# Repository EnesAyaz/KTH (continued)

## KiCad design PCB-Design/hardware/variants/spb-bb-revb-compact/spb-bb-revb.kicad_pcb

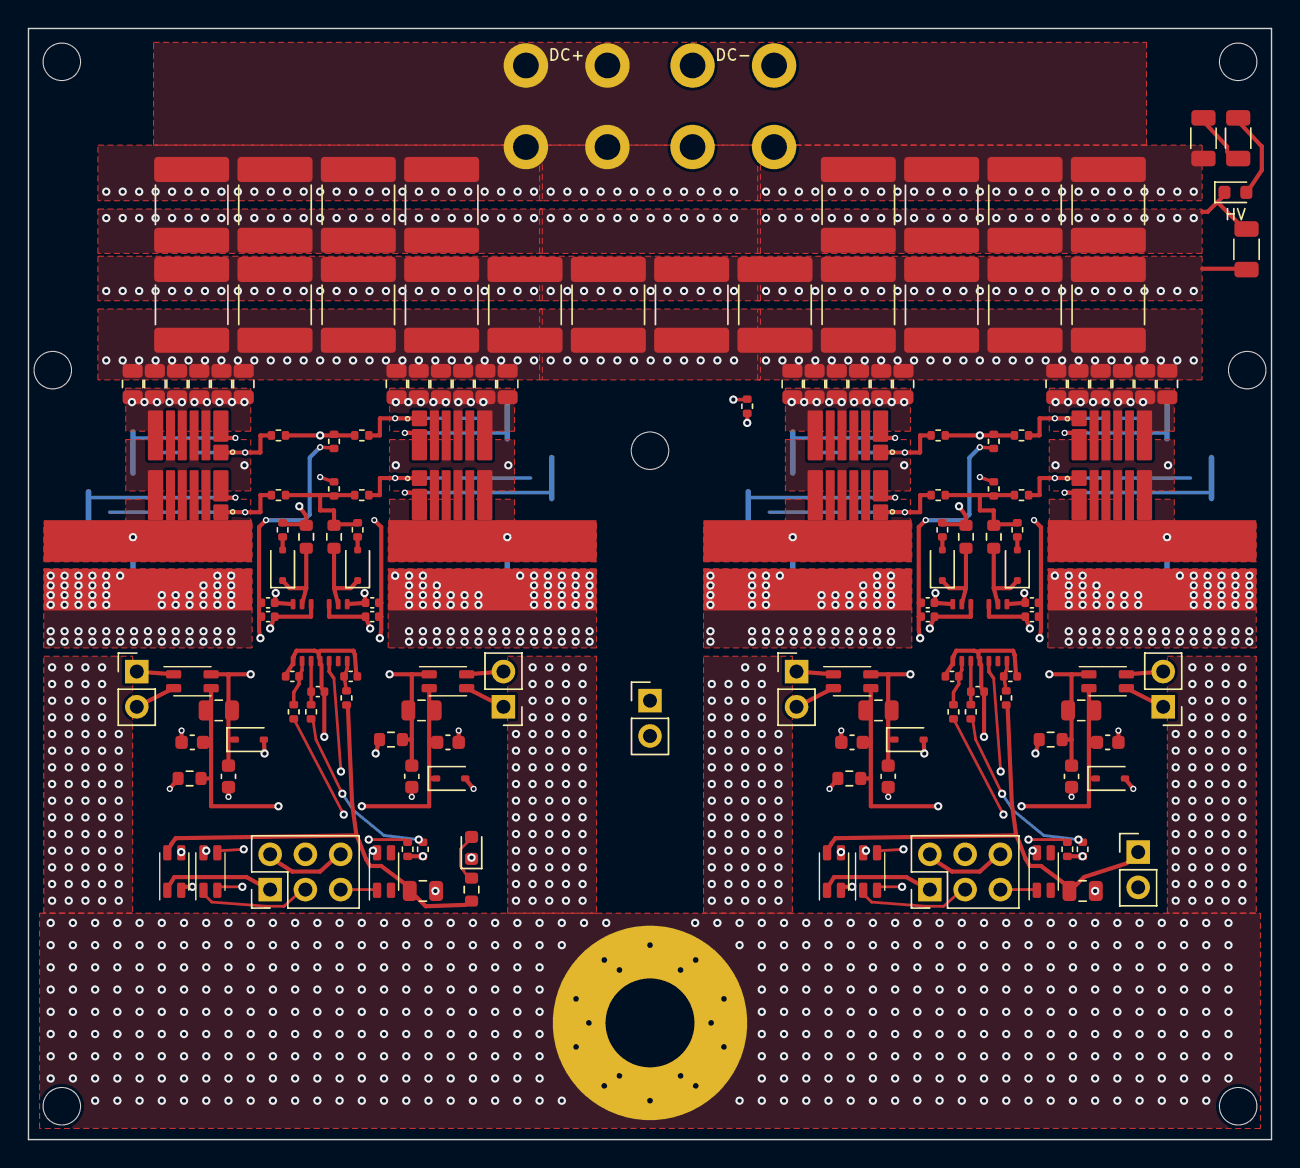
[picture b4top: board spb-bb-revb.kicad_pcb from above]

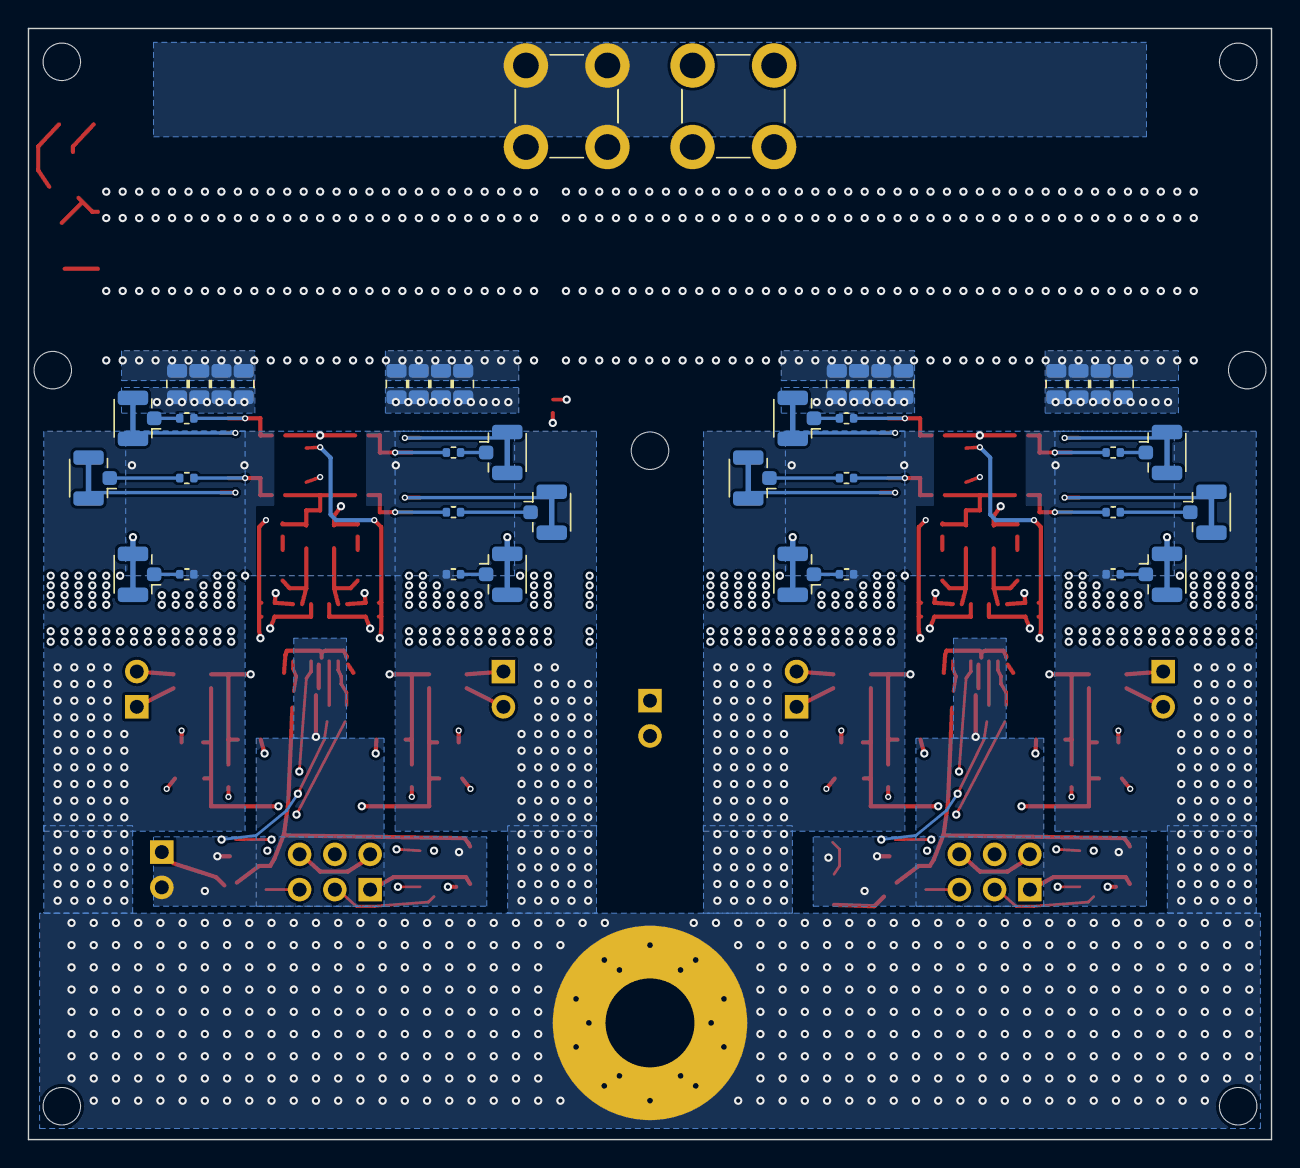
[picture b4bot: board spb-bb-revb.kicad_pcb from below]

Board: 4 copper layers, 89.5 x 80.0 mm, 204 parts (42 on the bottom side), 89 nets.

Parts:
C1, C2, C3, C4, C5, C6, C7, C8, C9, C10, C11, C12, C27, C28, C29, C30, C31, C32, C33, C34, C35, C36, C37, C38, C39, C40, C41, C42, C43, C44, C45, C46, C61, C62, C63, C64, C65, C66, C67, C68: 1uF 100V X7S; C_0805_2012Metric_TightCrtYd
C13, C14, C15, C16, C47, C48, C49, C50: 1uF 16V X7R 0402; C_0402_1005Metric
C17, C18, C51, C52: 100pF C0G 0402; C_0402_1005Metric
C19, C53: 22nF 25V X7R 0402; C_0402_1005Metric
C20, C23, C54, C57: 4.7uF 25V X7R 0805; C_0805_2012Metric
C21, C22, C24, C25, C55, C56, C58, C59: 4.7uF 16V X5R 0603; C_0603_1608Metric
C26, C60: 4.7uF 25V X7R 0805 (12 V); C_0805_2012Metric
C69, C70, C71, C72, C73, C74, C75, C76, C77, C78, C79, C80, C81, C82, C83, C84, C85, C86, C87, C88: 22uF 100V X7S 2220; C_2220_5750Metric_TightCrtYd
D1, D2, D6, D7: PMEG3020EJ; D_SOD-323F
D3, D4, D8, D9: BZX384-C5V1; D_SOD-323
D5: green 0603 (12 V); LED_0603_1608Metric
D10: red 0603 (DC link present); LED_0603_1608Metric
H1, H2, H3, H4: M2.5 insulated; MountingHole_2.7mm_M2.5
H5, H6, H7: M2.5 heatsink spreader; MountingHole_2.7mm_M2.5
HS1: Fischer LAM 4 (100 mm) + spreader; HS_LAM4K10012_revb
J1: DC+; Wuerth_REDCUBE-THR_WP-THRBU_74650174_THR
J2: DC-; Wuerth_REDCUBE-THR_WP-THRBU_74650174_THR
J3, J12: V_ISO,HS in: 1 +, 2 -; PinHeader_1x02_P2.54mm_Vertical
J4, J13: V_ISO,LS in: 1 +, 2 -; PinHeader_1x02_P2.54mm_Vertical
J5: CTRL1: 1 12V 2 GND 3 PWM_H 4 PWM_L 5 DIS 6 GND; PinHeader_2x03_P2.54mm_Vertical
J6: U.FL H1; U.FL_Hirose_U.FL-R-SMT-1_Vertical
J7: U.FL L1; U.FL_Hirose_U.FL-R-SMT-1_Vertical
J8: U.FL D1; U.FL_Hirose_U.FL-R-SMT-1_Vertical
J9: U.FL H2; U.FL_Hirose_U.FL-R-SMT-1_Vertical
J10: U.FL L2; U.FL_Hirose_U.FL-R-SMT-1_Vertical
J11: U.FL D2; U.FL_Hirose_U.FL-R-SMT-1_Vertical
J14: CTRL2: 1 12V 2 GND 3 PWM_H 4 PWM_L 5 DIS 6 GND; PinHeader_2x03_P2.54mm_Vertical
J15: FAN 12V: 1 +12V, 2 GND; PinHeader_1x02_P2.54mm_Vertical
J16: U.FL H3; U.FL_Hirose_U.FL-R-SMT-1_Vertical
J17: U.FL L3; U.FL_Hirose_U.FL-R-SMT-1_Vertical
J18: U.FL D3; U.FL_Hirose_U.FL-R-SMT-1_Vertical
J19: U.FL H4; U.FL_Hirose_U.FL-R-SMT-1_Vertical
J20: U.FL L4; U.FL_Hirose_U.FL-R-SMT-1_Vertical
J21: U.FL D4; U.FL_Hirose_U.FL-R-SMT-1_Vertical
J22: AC; AC_BOLT_M6
J23: 1:NTC 2:DC- (LS domain!); PinHeader_1x02_P2.54mm_Vertical
L1, L2, L3, L4, L5, L6, L7, L8, L9, L10: WE-CNSW 744232601; L_CommonMode_Wurth_WE-CNSW-1206
Q1, Q2, Q3, Q4, Q5, Q6, Q7, Q8: EPC2361
R1, R25: 0R5 1% (R_G HL); R_0402_1005Metric
R2, R26: 0R5 1% (R_G HR); R_0402_1005Metric
R3, R27: 0R5 1% (R_G LL); R_0402_1005Metric
R4, R28: 0R5 1% (R_G LR); R_0402_1005Metric
R5, R29: 10k 1% (HS gate pull-down); R_0402_1005Metric
R6, R30: 10k 1% (LS gate pull-down); R_0402_1005Metric
R7, R31: 0R75 1% (R_ON,A); R_0603_1608Metric
R8, R32: 0R (R_OFF,A); R_0402_1005Metric
R9, R33: 0R75 1% (R_ON,B); R_0603_1608Metric
R10, R34: 0R (R_OFF,B); R_0402_1005Metric
R11, R35: 47R 1% (INA); R_0402_1005Metric
R12, R36: 47R 1% (INB); R_0402_1005Metric
R13, R37: 3k 1% (RVDDI); R_0402_1005Metric
R14, R15, R38, R39: 150R 1% 0603 (bias, <= 82 mW); R_0603_1608Metric
R16, R40: 10k (PWM_H pull-down); R_0402_1005Metric
R17, R41: 10k (PWM_L pull-down); R_0402_1005Metric
R18: 4.7k (LED); R_0603_1608Metric
R19, R22, R42, R45: 0R (V_GS HS); R_0402_1005Metric
R20, R23, R43, R46: 0R (V_GS LS); R_0402_1005Metric
R21, R24, R44, R47: 953R 1% (V_DS LS, 20:1 into 50 R); R_0402_1005Metric
R48, R49: 68k 1206 (HV LED); R_1206_3216Metric
R50: 100k 1206 (bleeder); R_1206_3216Metric
RS1, RS2, RS3, RS4: UFCS-R001; PMK_UFCS_R001
RT1: NTC 10k B3380; R_0402_1005Metric
U1, U2: 2EDF7275K; 2EDF7275K_PG-TFLGA-13-4

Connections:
+12V1: C26.1, L3.2, R13.1, R18.1
+12V2: C60.1, J15.1, L8.2, R37.1
C_12V1: J5.1, L3.1
C_12V2: J14.1, L8.1
C_DIS1: J5.5, L5.1
C_DIS2: J14.5, L10.1
C_GND1: J5.2, J5.6, L3.4
C_GND2: J14.2, J14.6, L8.4
C_PWMH1: J5.3, L4.1
C_PWMH2: J14.3, L9.1
C_PWML1: J5.4, L4.4
C_PWML2: J14.4, L9.4
DCN: C1.2, C2.2, C3.2, C4.2, C5.2, C6.2, C7.2, C8.2, C9.2, C10.2, C11.2, C12.2, C27.1, C28.1, C29.1, C30.1, C31.1, C32.1, C33.1, C34.1, C35.2, C36.2, C37.2, C38.2, C39.2, C40.2, C41.2, C42.2, C43.2, C44.2, C45.2, C46.2, C61.1, C62.1, C63.1, C64.1, C65.1, C66.1, C67.1, C68.1, C69.1, C70.1, C71.1, C72.1, C73.1, C74.1, C75.1, C76.1, C77.1, C78.1, C79.1, C80.1, C81.1, C82.1, C83.1, C84.1, C85.1, C86.1, C87.1, C88.1, D10.1, J2.1, J23.2, R50.2, RS1.2, RS2.2, RS3.2, RS4.2, RT1.1
DCP: C1.1, C2.1, C3.1, C4.1, C5.1, C6.1, C7.1, C8.1, C9.1, C10.1, C11.1, C12.1, C27.2, C28.2, C29.2, C30.2, C31.2, C32.2, C33.2, C34.2, C35.1, C36.1, C37.1, C38.1, C39.1, C40.1, C41.1, C42.1, C43.1, C44.1, C45.1, C46.1, C61.2, C62.2, C63.2, C64.2, C65.2, C66.2, C67.2, C68.2, C69.2, C70.2, C71.2, C72.2, C73.2, C74.2, C75.2, C76.2, C77.2, C78.2, C79.2, C80.2, C81.2, C82.2, C83.2, C84.2, C85.2, C86.2, C87.2, C88.2, J1.1, Q1.3, Q1.5, Q1.7, Q2.3, Q2.5, Q2.7, Q5.3, Q5.5, Q5.7, Q6.3, Q6.5, Q6.7, R48.1, R50.1
DIS1: L5.2, U1.5
DIS2: L10.2, U2.5
GH_L1: Q1.1, R1.1, R19.2
GH_L2: Q5.1, R25.1, R42.2
GH_R1: Q2.1, R2.2, R22.1
GH_R2: Q6.1, R26.2, R45.1
GH_STAR1: R1.2, R2.1, R5.2, R7.2, R8.2
GH_STAR2: R25.2, R26.1, R29.2, R31.2, R32.2
GL_L1: Q3.1, R3.1, R20.2
GL_L2: Q7.1, R27.1, R43.2
GL_R1: Q4.1, R4.2, R23.1
GL_R2: Q8.1, R28.2, R46.1
GL_STAR1: R3.2, R4.1, R6.1, R9.2, R10.2
GL_STAR2: R27.2, R28.1, R30.1, R33.2, R34.2
GNDI1: C17.1, C18.2, C19.2, C26.2, D5.1, L3.3, R16.1, R17.1, U1.1, U1.4
GNDI2: C51.1, C52.2, C53.2, C60.2, J15.2, L8.3, R40.1, R41.1, U2.1, U2.4
HVA: R48.2, R49.1
HVB: D10.2, R49.2
INA1: C17.2, R11.2, U1.2
INA2: C51.2, R35.2, U2.2
INB1: C18.1, R12.2, U1.3
INB2: C52.1, R36.2, U2.3
KH1: C13.1, C14.1, C21.1, C22.1, D3.2, J6.2, J9.2, Q1.2, Q2.2, R5.1, R14.1
KH2: C47.1, C48.1, C55.1, C56.1, D8.2, J16.2, J19.2, Q5.2, Q6.2, R29.1, R38.1
KL1: C15.2, C16.2, C24.1, C25.2, D4.2, J7.2, J10.2, Q3.2, Q4.2, R6.2, R15.1
KL2: C49.2, C50.2, C58.1, C59.2, D9.2, J17.2, J20.2, Q7.2, Q8.2, R30.2, R39.1
LEDA_12V1: D5.2, R18.2
LSRC1: J8.2, Q3.4, Q3.6, RS1.1
LSRC2: J11.2, Q4.4, Q4.6, RS2.1
LSRC3: J18.2, Q7.4, Q7.6, RS3.1
LSRC4: J21.2, Q8.4, Q8.6, RS4.1
NTC: J23.1, RT1.2
OFFA1: D1.2, R8.1
OFFA2: D6.2, R32.1
OFFB1: D2.2, R10.1
OFFB2: D7.2, R34.1
OUTA1: D1.1, R7.1, U1.12
OUTA2: D6.1, R31.1, U2.12
OUTB1: D2.1, R9.1, U1.9
OUTB2: D7.1, R33.1, U2.9
PWM_H1: L4.2, R11.1, R16.2
PWM_H2: L9.2, R35.1, R40.2
PWM_L1: L4.3, R12.1, R17.2
PWM_L2: L9.3, R36.1, R41.2
SW: J22.1, Q1.4, Q1.6, Q2.4, Q2.6, Q3.3, Q3.5, Q3.7, Q4.3, Q4.5, Q4.7, Q5.4, Q5.6, Q6.4, Q6.6, Q7.3, Q7.5, Q7.7, Q8.3, Q8.5, Q8.7, R21.2, R24.1, R44.2, R47.1
UFL_D1: J8.1, R21.1
UFL_D2: J11.1, R24.2
UFL_D3: J18.1, R44.1
UFL_D4: J21.1, R47.2
UFL_H1: J6.1, R19.1
UFL_H2: J9.1, R22.2
UFL_H3: J16.1, R42.1
UFL_H4: J19.1, R45.2
UFL_L1: J7.1, R20.1
UFL_L2: J10.1, R23.2
UFL_L3: J17.1, R43.1
UFL_L4: J20.1, R46.2
VDDA1: C13.2, C20.2, C21.2, D3.1, L1.2, U1.13
VDDA2: C47.2, C54.2, C55.2, D8.1, L6.2, U2.13
VDDB1: C16.1, C23.2, C25.1, D4.1, L2.4, U1.10
VDDB2: C50.1, C57.2, C59.1, D9.1, L7.4, U2.10
VDDI1: C19.1, R13.2, U1.7
VDDI2: C53.1, R37.2, U2.7
VEEA1: C14.2, C20.1, C22.2, L1.3, R14.2, U1.11
VEEA2: C48.2, C54.1, C56.2, L6.3, R38.2, U2.11
VEEB1: C15.1, C23.1, C24.2, L2.1, R15.2, U1.8
VEEB2: C49.1, C57.1, C58.2, L7.1, R39.2, U2.8
VINA_N1: J3.2, L1.4
VINA_N2: J12.2, L6.4
VINA_P1: J3.1, L1.1
VINA_P2: J12.1, L6.1
VINB_N1: J4.2, L2.2
VINB_N2: J13.2, L7.2
VINB_P1: J4.1, L2.3
VINB_P2: J13.1, L7.3
